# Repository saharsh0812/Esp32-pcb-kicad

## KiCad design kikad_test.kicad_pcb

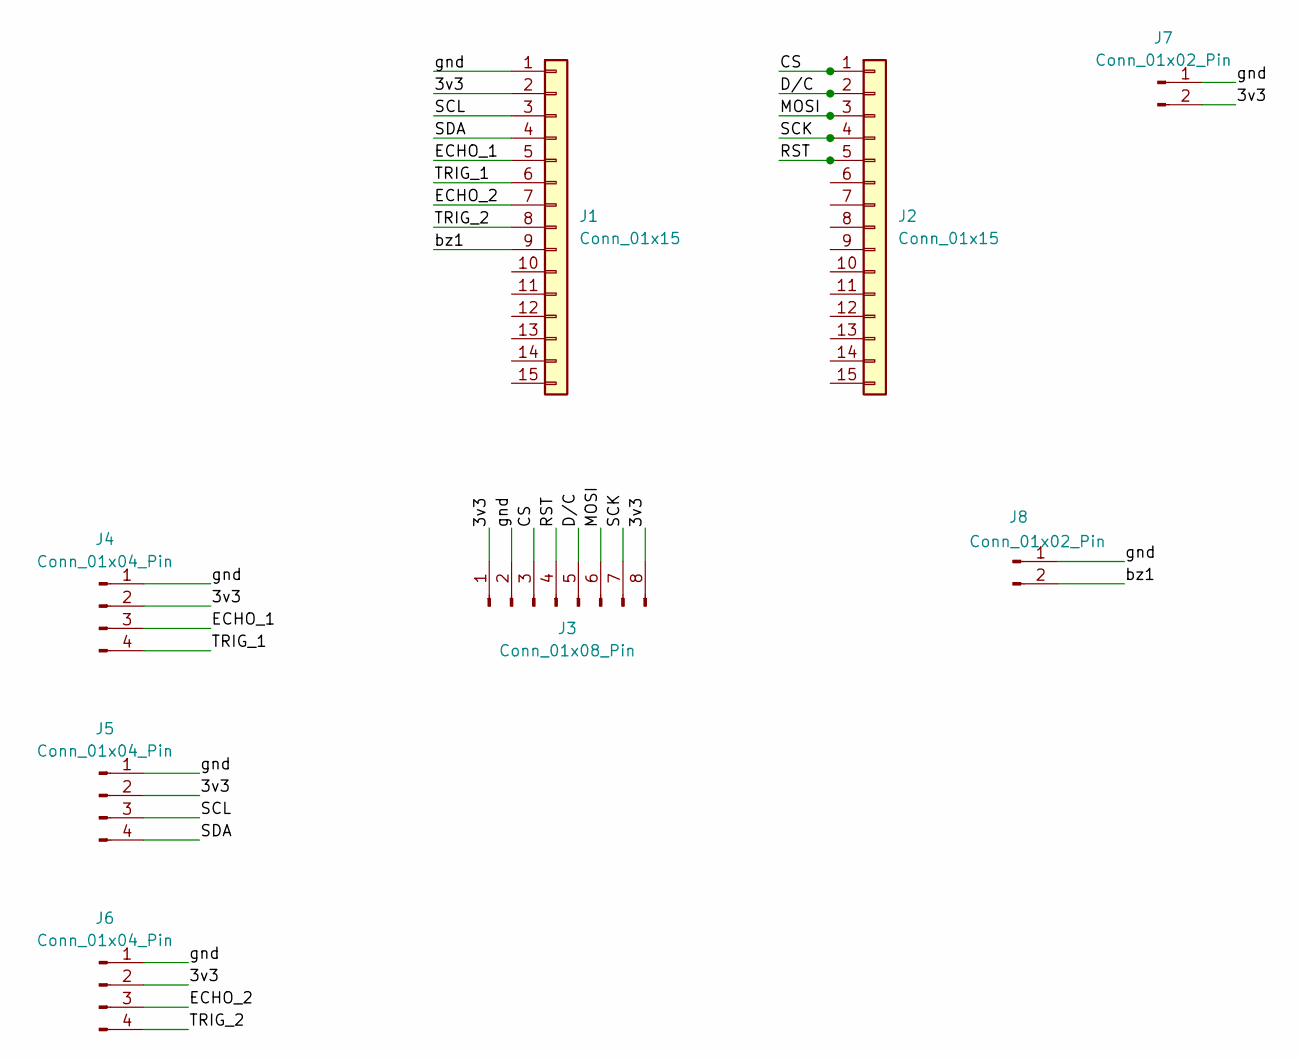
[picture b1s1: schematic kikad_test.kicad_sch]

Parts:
J1, J2: Conn_01x15; PinSocket_1x15_P2.54mm_Vertical
J3: Conn_01x08_Pin; PinSocket_1x08_P2.54mm_Vertical
J4, J5, J6: Conn_01x04_Pin; PinSocket_1x04_P2.54mm_Vertical
J7: Conn_01x02_Pin; TerminalBlock_Phoenix_MKDS-1,5-2_1x02_P5.00mm_Horizontal
J8: Conn_01x02_Pin; PinSocket_1x02_P2.54mm_Vertical

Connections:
/3v3: J1.2, J3.1, J3.8, J4.2, J5.2, J6.2, J7.2
/CS: J2.1, J3.3
/D/C: J2.2, J3.5
/ECHO_1: J1.5, J4.3
/ECHO_2: J1.7, J6.3
/MOSI: J2.3, J3.6
/RST: J2.5, J3.4
/SCK: J2.4, J3.7
/SCL: J1.3, J5.3
/SDA: J1.4, J5.4
/TRIG_1: J1.6, J4.4
/TRIG_2: J1.8, J6.4
/bz1: J1.9, J8.2
/gnd: J1.1, J3.2, J4.1, J5.1, J6.1, J7.1, J8.1

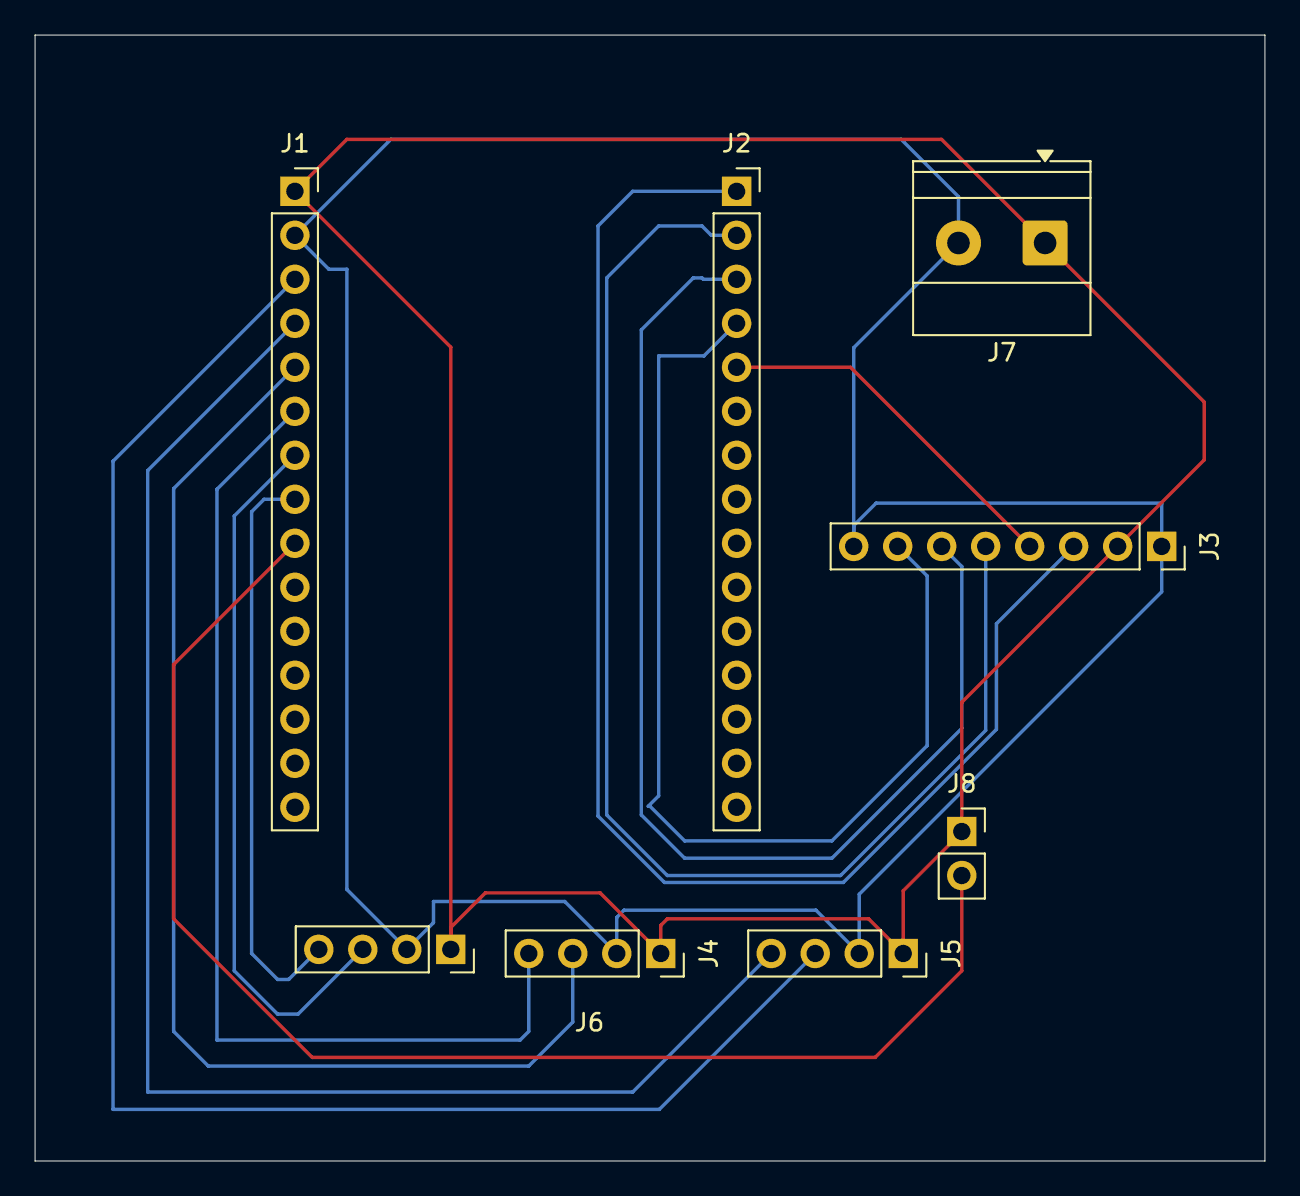
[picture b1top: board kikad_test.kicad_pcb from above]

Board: 2 copper layers, 71.0 x 65.0 mm, 8 parts (0 on the bottom side), 14 nets.
